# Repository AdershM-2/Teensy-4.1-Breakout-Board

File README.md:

# Teensy 4.1 Breakout Board
 A simple Breakout board schematic for teensy 4.1 to attach pluggable screw terminals (2.54mm pitch)

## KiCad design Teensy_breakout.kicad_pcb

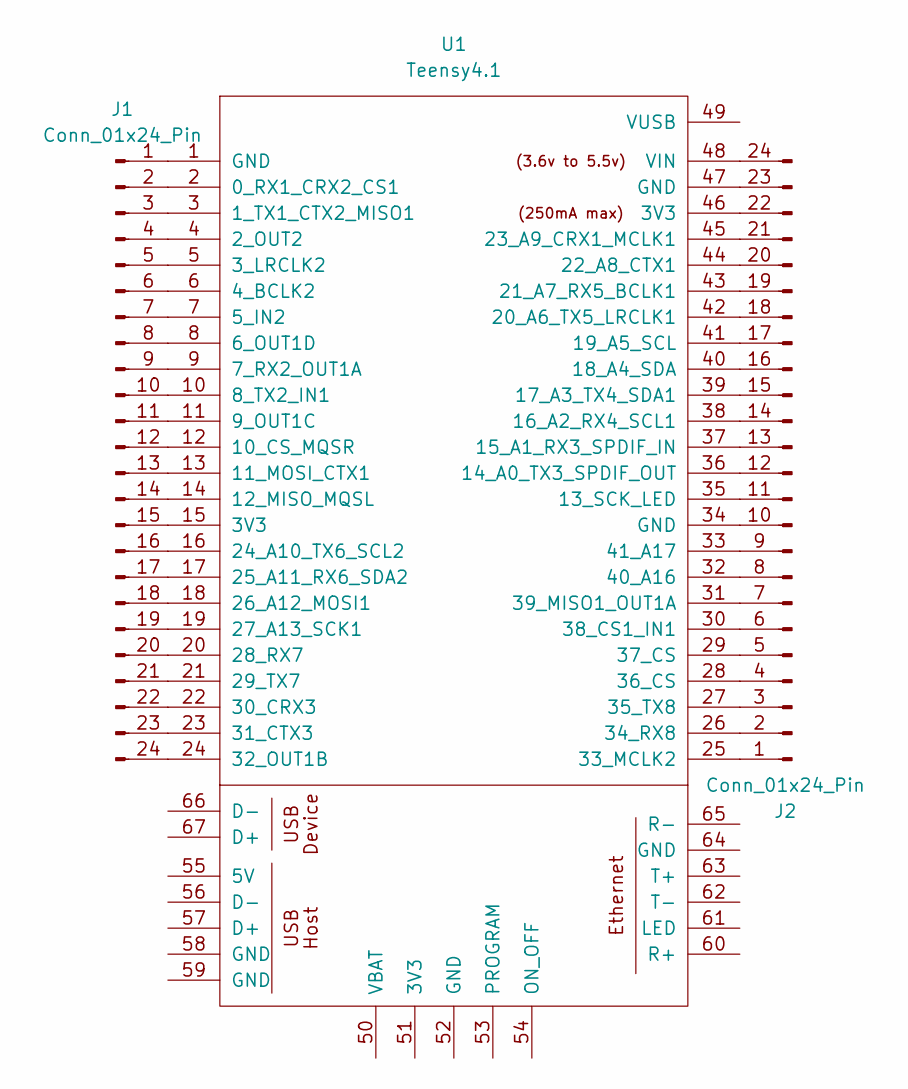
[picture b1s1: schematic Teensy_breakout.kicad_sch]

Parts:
J1, J2: Conn_01x24_Pin; PinHeader_1x24_P2.54mm_Vertical
U1: Teensy4.1; Teensy41

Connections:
unnamed: J1.1, U1.1 (GND)
unnamed: J1.2, U1.2 (0_RX1_CRX2_CS1)
unnamed: J1.3, U1.3 (1_TX1_CTX2_MISO1)
unnamed: J1.4, U1.4 (2_OUT2)
unnamed: J1.5, U1.5 (3_LRCLK2)
unnamed: J1.6, U1.6 (4_BCLK2)
unnamed: J1.7, U1.7 (5_IN2)
unnamed: J1.8, U1.8 (6_OUT1D)
unnamed: J1.9, U1.9 (7_RX2_OUT1A)
unnamed: J1.10, U1.10 (8_TX2_IN1)
unnamed: J1.11, U1.11 (9_OUT1C)
unnamed: J1.12, U1.12 (10_CS_MQSR)
unnamed: J1.13, U1.13 (11_MOSI_CTX1)
unnamed: J1.14, U1.14 (12_MISO_MQSL)
unnamed: J1.15, U1.15 (3V3)
unnamed: J1.16, U1.16 (24_A10_TX6_SCL2)
unnamed: J1.17, U1.17 (25_A11_RX6_SDA2)
unnamed: J1.18, U1.18 (26_A12_MOSI1)
unnamed: J1.19, U1.19 (27_A13_SCK1)
unnamed: J1.20, U1.20 (28_RX7)
unnamed: J1.21, U1.21 (29_TX7)
unnamed: J1.22, U1.22 (30_CRX3)
unnamed: J1.23, U1.23 (31_CTX3)
unnamed: J1.24, U1.24 (32_OUT1B)
unnamed: J2.1, U1.25 (33_MCLK2)
unnamed: J2.2, U1.26 (34_RX8)
unnamed: J2.3, U1.27 (35_TX8)
unnamed: J2.4, U1.28 (36_CS)
unnamed: J2.5, U1.29 (37_CS)
unnamed: J2.6, U1.30 (38_CS1_IN1)
unnamed: J2.7, U1.31 (39_MISO1_OUT1A)
unnamed: J2.8, U1.32 (40_A16)
unnamed: J2.9, U1.33 (41_A17)
unnamed: J2.10, U1.34 (GND)
unnamed: J2.11, U1.35 (13_SCK_LED)
unnamed: J2.12, U1.36 (14_A0_TX3_SPDIF_OUT)
unnamed: J2.13, U1.37 (15_A1_RX3_SPDIF_IN)
unnamed: J2.14, U1.38 (16_A2_RX4_SCL1)
unnamed: J2.15, U1.39 (17_A3_TX4_SDA1)
unnamed: J2.16, U1.40 (18_A4_SDA)
unnamed: J2.17, U1.41 (19_A5_SCL)
unnamed: J2.18, U1.42 (20_A6_TX5_LRCLK1)
unnamed: J2.19, U1.43 (21_A7_RX5_BCLK1)
unnamed: J2.20, U1.44 (22_A8_CTX1)
unnamed: J2.21, U1.45 (23_A9_CRX1_MCLK1)
unnamed: J2.22, U1.46 (3V3)
unnamed: J2.23, U1.47 (GND)
unnamed: J2.24, U1.48 (VIN)

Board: 2 copper layers, 3 parts (0 on the bottom side), 48 nets, no tracks yet.

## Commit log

2024-08-29 Added the files
